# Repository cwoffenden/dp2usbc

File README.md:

DisplayPort to USB-C Carrier
============================

This project allows USB-C monitors to be connected via DisplayPort. Specifically, this was to connect a Mac [External Graphics Development Kit](https://developer.apple.com/development-kit/external-graphics/) to the USB-C only [LG Ultrafine 4k](https://www.lg.com/us/monitors/lg-22MD4KA-B-4k-uhd-led-monitor), but should work with other eGPU and monitor configurations.

Various designs of this have been in use since September 2017, initially with a single Ultrafine, but now running a multi-monitor setup for times when only 12'288 horizontal pixels will do! It works with both macOS and Windows running on the same machine (under Boot Camp).

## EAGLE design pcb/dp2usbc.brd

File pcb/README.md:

Schematic and board layout for [CadSoft Eagle](http://www.cadsoftusa.com/). The project file is for 6.5 but should work in newer versions.

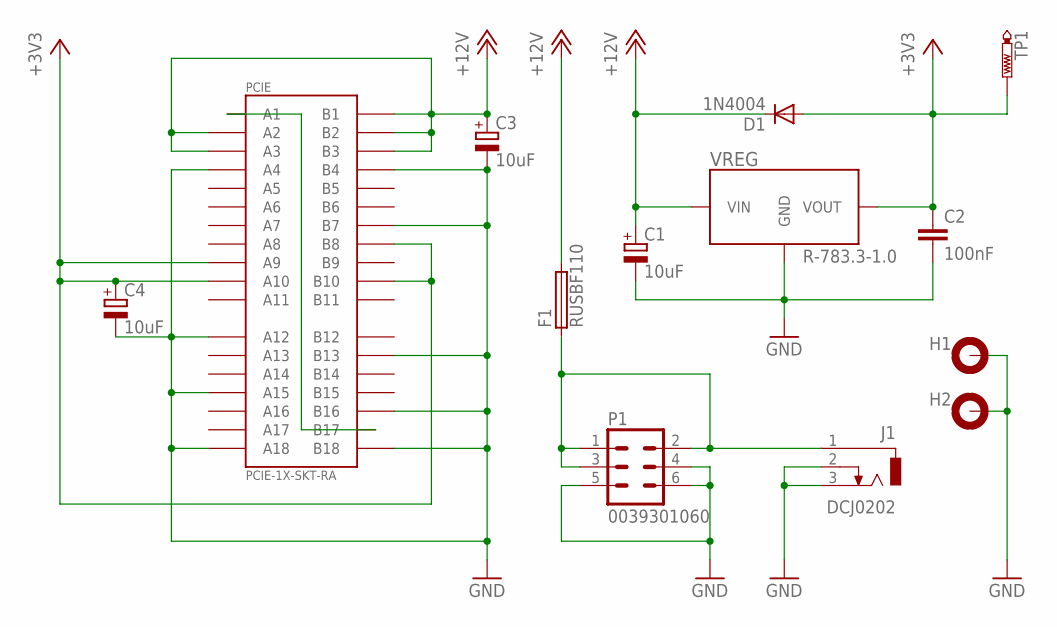
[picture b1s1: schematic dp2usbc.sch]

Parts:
C1, C3, C4: 10uF; E1,8-4
C2: 100nF; C025-024X044
D1: 1N4004; DO41-10
F1: RUSBF110; LITTLEFUSE
H1, H2: MOUNT-PAD-ROUND3.2; 3,2-PAD
J1: DCJ0202
P1: 0039301060
PCIE: PCIE-1X-SKT-RA
TP1: PTR1B1,27; B1,27
VREG: R-783.3-1.0; VREG-RECOM-78*

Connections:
+3V3: C2.1, C4.+, D1.A, PCIE.A9, PCIE.A10, PCIE.B8, PCIE.B10, TP1.TP, VREG.VOUT
+12V: C1.+, C3.+, D1.C, F1.2, PCIE.A2, PCIE.A3, PCIE.B1, PCIE.B2, PCIE.B3, VREG.VIN
B11: PCIE.B11
GND: C1.-, C2.2, C3.-, C4.-, H1.B3,2, H2.B3,2, J1.2, J1.3, P1.4, P1.5, P1.6, PCIE.A4, PCIE.A12, PCIE.A15, PCIE.A18, PCIE.B4, PCIE.B7, PCIE.B13, PCIE.B16, PCIE.B18, VREG.GND
unnamed: PCIE.A1, PCIE.B17
unnamed: F1.1, J1.1, P1.1, P1.2, P1.3

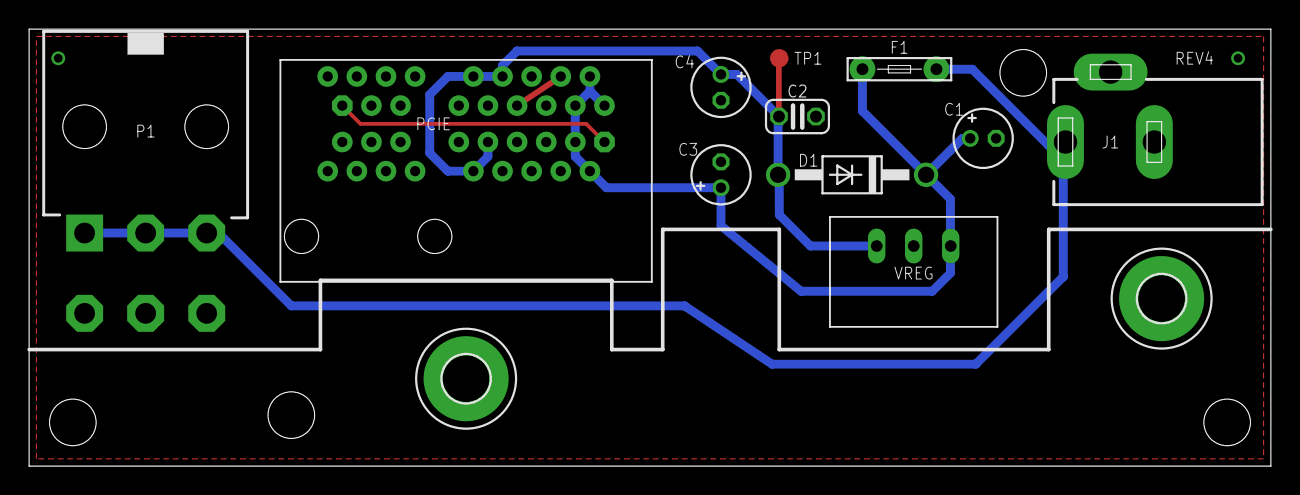
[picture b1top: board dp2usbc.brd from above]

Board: 2 copper layers, 85.2 x 30.0 mm, 13 parts (0 on the bottom side), 5 nets.

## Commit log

2018-12-02 Added board layout.
2019-03-10 Added photos and screenshots.
2019-03-10 Added box CAD files. Updated description.
2019-03-10 STL now resides with Gerbers.
2019-06-09 Docs images now have relative paths

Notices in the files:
parts and their libraries:
con-molex-mini-fit: Copyright (C) 2011, Bob Starr
